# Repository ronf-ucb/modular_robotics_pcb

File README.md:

modular_robotics_pcb
====================

Board designs for the embedded modular robotics project

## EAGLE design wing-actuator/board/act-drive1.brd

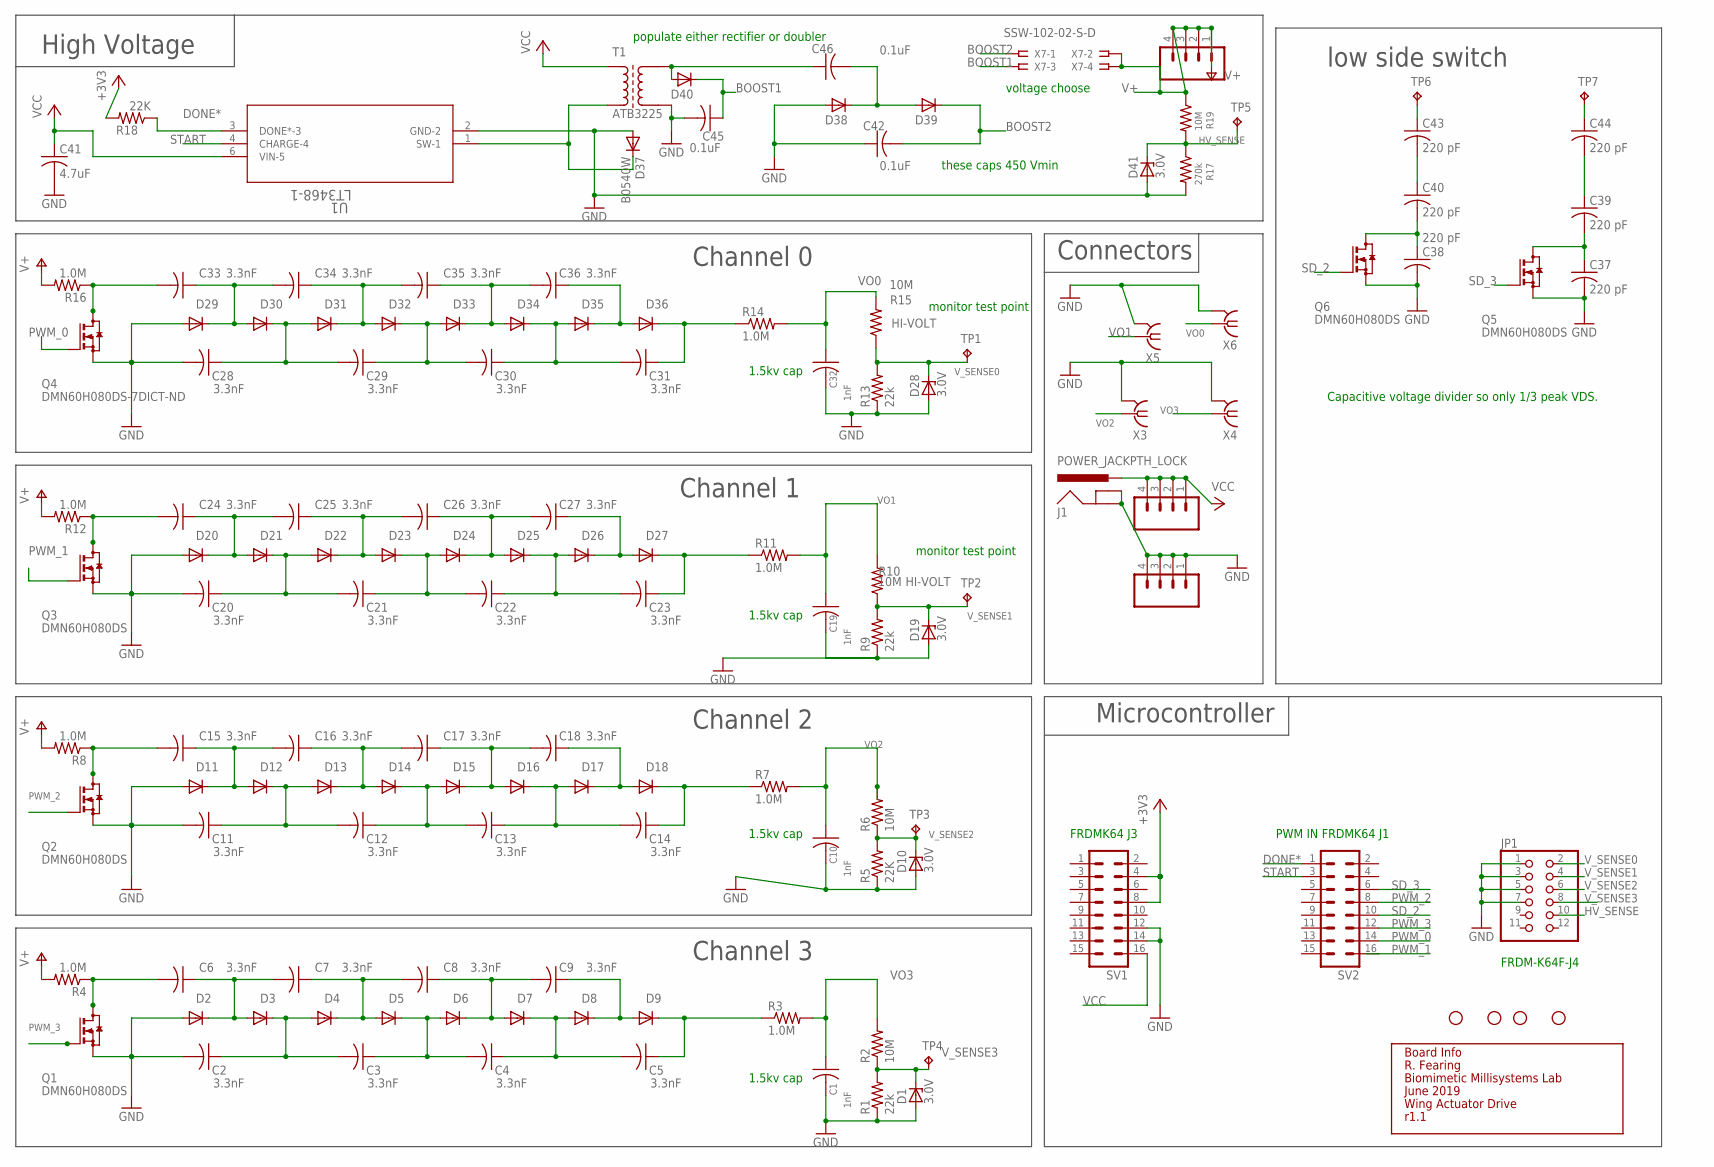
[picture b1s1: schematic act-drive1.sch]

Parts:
C1, C10, C19, C32: 1nF; C1206; DIGIKEY 399-7078-1-ND
C2, C3, C4, C5, C6, C7, C8, C9, C11, C12, C13, C14, C15, C16, C17, C18, C20, C21, C22, C23, C24, C25, C26, C27, C28, C29, C30, C31, C34, C35, C36: 3.3nF; C0805K
C33: 3.3nF; C0805K; DIGIKEY 399-5576-1-ND
C37, C38, C39, C40, C43, C44: 220 pF; C1206; DIGIKEY 311-4469-1-ND
C41: 4.7uF; C1206; DIGIKEY 399-1265-1-ND
C42, C45, C46: 0.1uF; C1206; DIGIKEY 445-7758-1-ND
D1, D10, D19: 3.0V; SOD80C
D2, D3, D4, D5, D6, D7, D8, D9, D11, D12, D13, D14, D15, D16, D17, D22, D23, D25, D26, D27, D30, D31, D32, D33, D34, D35, D36, D38, D39, D40: DIODE-SOD323-W; SOD323-W
D18, D20, D21, D24, D29: DIODE-SOD323-W; SOD323-W; DIGIKEY DA2JF8100LCT-ND
D28, D41: 3.0V; SOD80C; DIGIKEY MM3Z3V0ST1GOSCT-ND
D37: B0540W; SOD123; DIGIKEY B0540W-FDICT-ND
H1, H2, H3, H4: STAND-OFFTIGHT; STAND-OFF-TIGHT
I1: INFO
J1: POWER_JACKPTH_LOCK; POWER_JACK_PTH_LOCK; DIGIKEY CP-202A-ND
JP1: PINHD-2X6; 2X06
JP2, JP3, JP4: M04LOCK; 1X04_LOCK
Q1, Q2, Q3: BSS123; SOT23; PART# DMN60H080DS
Q4: BSS123; SOT23; DIGIKEY DMN60H080DS-7DICT-ND
Q5, Q6: BSS123; SOT23; PART# DMN60H080DS; DIGIKEY DMN60H080DS-7DICT-ND
R1, R9: 22k; R1206
R2, R6, R10, R15: 10M; R2010; DIGIKEY CHV2010-FX-1005ELFCT-ND
R3, R4, R7, R8, R11, R12, R14, R16: 1.0M; R1206; DIGIKEY P1.0MECT-ND
R5, R18: 22K; R1206
R13: 22k; R1206; DIGIKEY P22KECT-ND
R17: 270k; R1206; DIGIKEY P270KECT-ND
R19: 10M; R1206; DIGIKEY P10MECT-ND
SV1, SV2: ML16; DIGIKEY ED10523-ND
T1: ATB3225; XFMR3225; DIGIKEY 445-8636-1-ND
TP1, TP2, TP3, TP4: TPTP10SQ; TP10SQ
TP5, TP6, TP7: TPTP20SQ; TP20SQ
U1: LT3468-1; TSOT-23_S5; DIGIKEY LT3468ES5#TRMPBFCT-ND
X3, X4, X6: SMA-142-0701-801/806; J502-ND-142-0701-801/806
X5: SMA-142-0701-801/806; J502-ND-142-0701-801/806; DIGIKEY J502-ND
X7: SSW-102-02-S-D

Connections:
+3V3: R18.2, SV1.4, SV1.8
BOOST: C46.2, D38.C, D39.A
BOOST1: C45.1, D40.C, X7.3
BOOST2: C42.2, D39.C, X7.1
DONE*: R18.1, SV2.1, U1.3 (DONE*-3)
GND: C1.2, C2.2, C10.2, C11.2, C19.2, C20.2, C28.2, C32.2, C37.2, C38.2, C41.2, C42.1, C45.2, D1.A, D2.A, D10.A, D11.A, D19.A, D20.A, D28.A, D29.A, D37.A, D38.A, D41.A, J1.GND, J1.GNDBREAK, JP1.1, JP1.3, JP1.5, JP1.7, JP2.1, JP2.2, JP2.3, JP2.4, Q1.2 (S), Q2.2 (S), Q3.2 (S), Q4.2 (S), Q5.2 (S), Q6.2 (S), R1.1, R5.1, R9.1, R13.1, R17.2, SV1.12, SV1.14, T1.S3, U1.2 (GND-2), X3.G@1 (2), X3.G@2 (2), X3.G@3 (2), X3.G@4 (2), X4.G@1 (2), X4.G@2 (2), X4.G@3 (2), X4.G@4 (2), X5.G@1 (2), X5.G@2 (2), X5.G@3 (2), X5.G@4 (2), X6.G@1 (2), X6.G@2 (2), X6.G@3 (2), X6.G@4 (2)
HV_SENSE: D41.C, JP1.10, R17.1, R19.2, TP5.TP
unnamed: C29.1, C30.2, D32.C, D33.A
unnamed: C33.1, C34.2, D29.C, D30.A
unnamed: C31.1, D36.C, R14.1
unnamed: C14.1, D18.C, R7.1
unnamed: C28.1, C29.2, D30.C, D31.A
unnamed: C46.1, D40.A, T1.S2
unnamed: C34.1, C35.2, D31.C, D32.A
unnamed: C33.2, Q4.3 (D), R16.1
unnamed: C23.1, D27.C, R11.1
unnamed: C35.1, C36.2, D33.C, D34.A
unnamed: C24.1, C25.2, D20.C, D21.A
unnamed: D37.C, T1.P4, U1.1 (SW-1)
unnamed: C20.1, C21.2, D21.C, D22.A
unnamed: C27.1, D26.C, D27.A
unnamed: C21.1, C22.2, D23.C, D24.A
unnamed: C22.1, C23.2, D25.C, D26.A
unnamed: C15.1, C16.2, D11.C, D12.A
unnamed: C11.1, C12.2, D12.C, D13.A
unnamed: C18.1, D17.C, D18.A
unnamed: C25.1, C26.2, D22.C, D23.A
unnamed: C26.1, C27.2, D24.C, D25.A
unnamed: C24.2, Q3.3 (D), R12.1
unnamed: C12.1, C13.2, D14.C, D15.A
unnamed: C13.1, C14.2, D16.C, D17.A
unnamed: C5.1, D9.C, R3.1
unnamed: C16.1, C17.2, D13.C, D14.A
unnamed: C17.1, C18.2, D15.C, D16.A
unnamed: C15.2, Q2.3 (D), R8.1
unnamed: C6.1, C7.2, D2.C, D3.A
unnamed: C2.1, C3.2, D3.C, D4.A
unnamed: C9.1, D8.C, D9.A
unnamed: C3.1, C4.2, D5.C, D6.A
unnamed: C4.1, C5.2, D7.C, D8.A
unnamed: C7.1, C8.2, D4.C, D5.A
unnamed: C8.1, C9.2, D6.C, D7.A
unnamed: C6.2, Q1.3 (D), R4.1
unnamed: C43.1, TP6.TP
unnamed: C40.1, C43.2
unnamed: C38.1, C40.2, Q6.3 (D)
unnamed: C44.1, TP7.TP
unnamed: C39.1, C44.2
unnamed: C37.1, C39.2, Q5.3 (D)
unnamed: C36.1, D35.C, D36.A
unnamed: C30.1, C31.2, D34.C, D35.A
PWM_0: Q4.1 (G), SV2.14
PWM_1: Q3.1 (G), SV2.16
PWM_2: Q2.1 (G), SV2.8
PWM_3: Q1.1 (G), SV2.12
SD_2: Q6.1 (G), SV2.10
SD_3: Q5.1 (G), SV2.6
START: SV2.3, U1.4 (CHARGE-4)
V+: JP4.1, JP4.2, JP4.3, JP4.4, R4.2, R8.2, R12.2, R16.2, R19.1, X7.2, X7.4
VCC: C41.1, J1.PWR, JP3.1, JP3.2, JP3.3, JP3.4, SV1.16, T1.P1, U1.6 (VIN-5)
VO0: C32.1, R14.2, R15.2, X6.1
VO1: C19.1, R10.2, R11.2, X5.1
VO2: C10.1, R6.2, R7.2, X3.1
VO3: C1.1, R2.2, R3.2, X4.1
V_SENSE0: D28.C, JP1.2, R13.2, R15.1, TP1.TP
V_SENSE1: D19.C, JP1.4, R9.2, R10.1, TP2.TP
V_SENSE2: D10.C, JP1.6, R5.2, R6.1, TP3.TP
V_SENSE3: D1.C, JP1.8, R1.2, R2.1, TP4.TP

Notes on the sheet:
High Voltage
Channel 0
Channel 1
Channel 2
Channel 3
Microcontroller
Connectors
PWM IN FRDMK64 J1
FRDM-K64F-J4
monitor test point
FRDMK64 J3
populate either rectifier or doubler
low side switch
Capacitive voltage divider so only 1/3 peak VDS.
voltage choose
these caps 450 Vmin
1.5kv cap

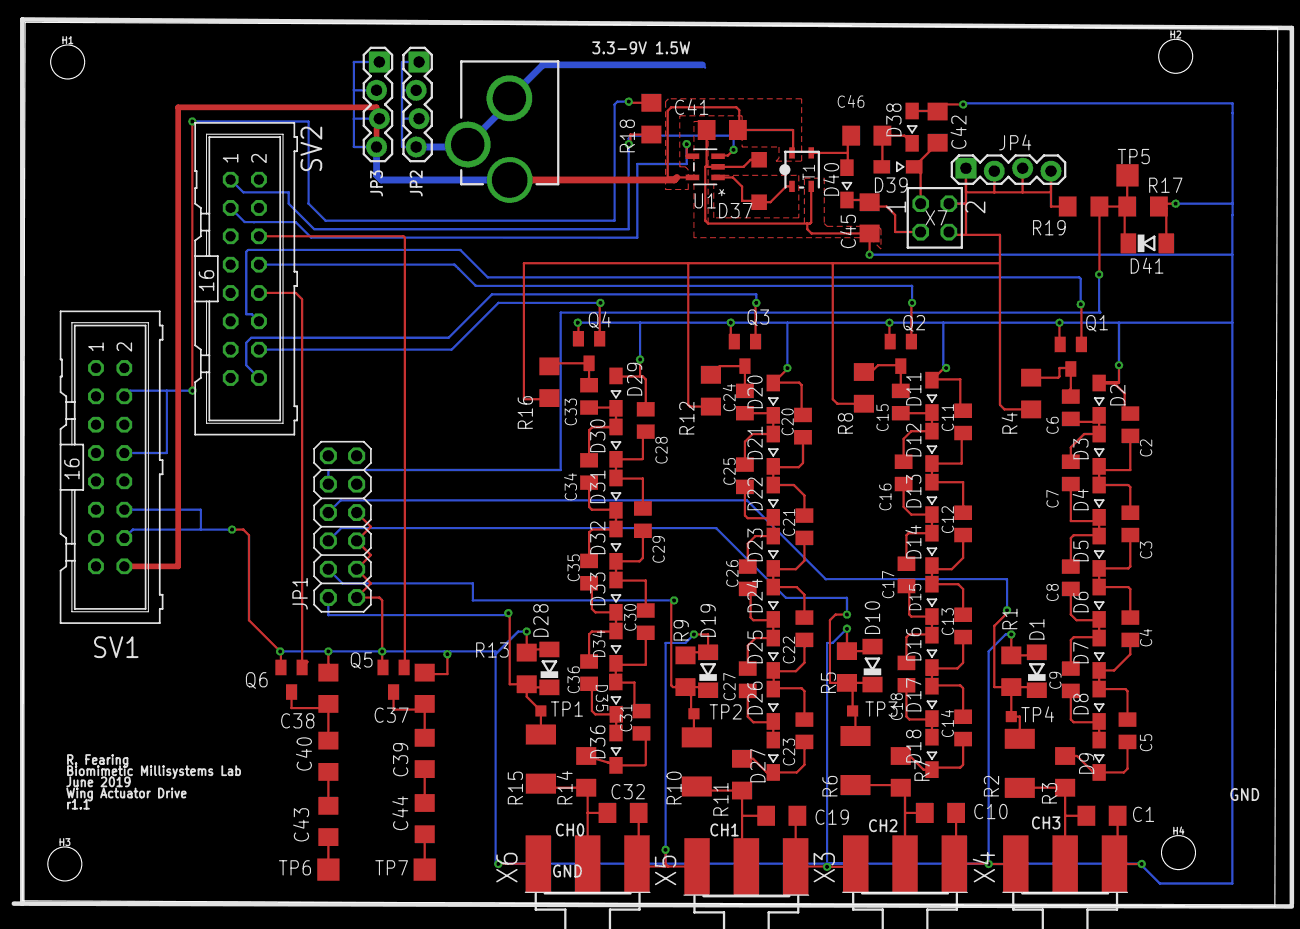
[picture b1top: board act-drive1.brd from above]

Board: 2 copper layers, 112.5 x 79.2 mm, 138 parts (0 on the bottom side), 68 nets.

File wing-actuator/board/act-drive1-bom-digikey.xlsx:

Qty | Value | Device | Package | Parts | Description | DIGIKEY | MOUSER
35 |  | DIODE-SOD323-W | SOD323-W | D2, D3, D4, D5, D6, D7, D8, D9, D11, D12, D13, D14, D15, D16, D17, D18,D19,D20,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 | DIODE | DA2JF8100LCT-ND
5 | 3.0V | ZENER-DIODESOD80C | SOD80C | D1, D10, D19, D28, D41 | Z-Diode | MM3Z3V0ST1GOSCT-ND
1 | B0540W | DIODE-SOD123 | SOD123 | D37 | DIODE | B0540W-FDICT-ND
8 | 1.0M | R-US_R1206 | R1206 | R3, R4, R7, R8, R11, R12, R14, R16 | RESISTOR, American symbol | P1.0MECT-ND
1 | 10M | R-US_R1206 | R1206 | R19 | RESISTOR, American symbol | P10MECT-ND
4 | 10M | R-US_R2010 | R2010 | R2, R6, R10, R15 | RESISTOR, American symbol | CHV2010-FX-1005ELFCT-ND
5 | 22K | R-US_R1206 | R1206 | R5, R18, R1, R9, R13 | RESISTOR, American symbol | P22KECT-ND
1 | 270k | R-US_R1206 | R1206 | R17 | RESISTOR, American symbol | P270KECT-ND
3 | 0.1uF 450V | C-USC1206 | C1206 | C42, C45, C46 | CAPACITOR, American symbol | 445-7758-1-ND
4 | 1nF 1k5V | C-USC1206 | C1206 | C1, C10, C19, C32 | CAPACITOR, American symbol | 399-7078-1-ND
6 | 220 pF, 1000V | C-USC1206 | C1206 | C37, C38, C39, C40, C43, C44 | CAPACITOR, American symbol | 311-4469-1-ND
32 | 3.3nF | C-USC0805K | C0805K | C2, C3, C4, C5, C6, C7, C8, C9, C11, C12, C13, C14, C15, C16, C17, C18, C20, C2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 | CAPACITOR, American symbol | 399-5576-1-ND
1 | 4.7uF | C-USC1206 | C1206 | C41 | CAPACITOR, American symbol | 399-1265-1-ND
1 | ATB3225 | ATB3225 | XFMR3225 | T1 | TDK ATB3225 xfmr 10:1 | 445-8636-1-ND
6 | BSS123 | BSS123 | SOT23 | Q1, Q2, Q3,Q4, Q5, Q6 | N-CHANNEL MOS FET | DMN60H080DS-7DICT-ND | 621-DMN60H080DS-7
1 | LT3468-1 | LT3468-1 | TSOT-23_S5 | U1 | Boost Converter | LT3468ES5#TRMPBFCT-ND
2 |  | ML16 | ML16 | SV1, SV2 | CONN HEADER VERT 16POS 2.54MM | ED10523-ND
2 |  |  |  | SV1P, SV2P | 16 Position Cable Assembly Rectangular Socket to Socket 1.50' | H3CCS-1618M-ND
1 | POWER_JACKPTH_LOCK | POWER_JACKPTH_LOCK | POWER_JACK_PTH_LOCK | J1 | Power Jack | CP-202A-ND
4 | SMA-142-0701-801/806 | SMA-142-0701-801/806 | J502-ND-142-0701-801/806 | X3, X4, X5, X6 | SMA 50 Ohm End Launch Jack Receptacle - Round Contact | J502-ND
1 | SSW-102-02-S-D | SSW-102-02-S-D | SSW-102-02-S-D | X7 | THROUGH-HOLE .025 SQ POST SOCKET"
4 | STAND-OFFTIGHT | STAND-OFFTIGHT | STAND-OFF-TIGHT | H1, H2, H3, H4 | Stand Off
4 | TPTP10SQ | TPTP10SQ | TP10SQ | TP1, TP2, TP3, TP4 | Test pad
3 | TPTP20SQ | TPTP20SQ | TP20SQ | TP5, TP6, TP7 | Test pad
3 |  | M04LOCK | 1X04_LOCK | JP2, JP3, JP4 | Header 4
1 |  | PINHD-2X6 | 2X06 | JP1 | PIN HEADER

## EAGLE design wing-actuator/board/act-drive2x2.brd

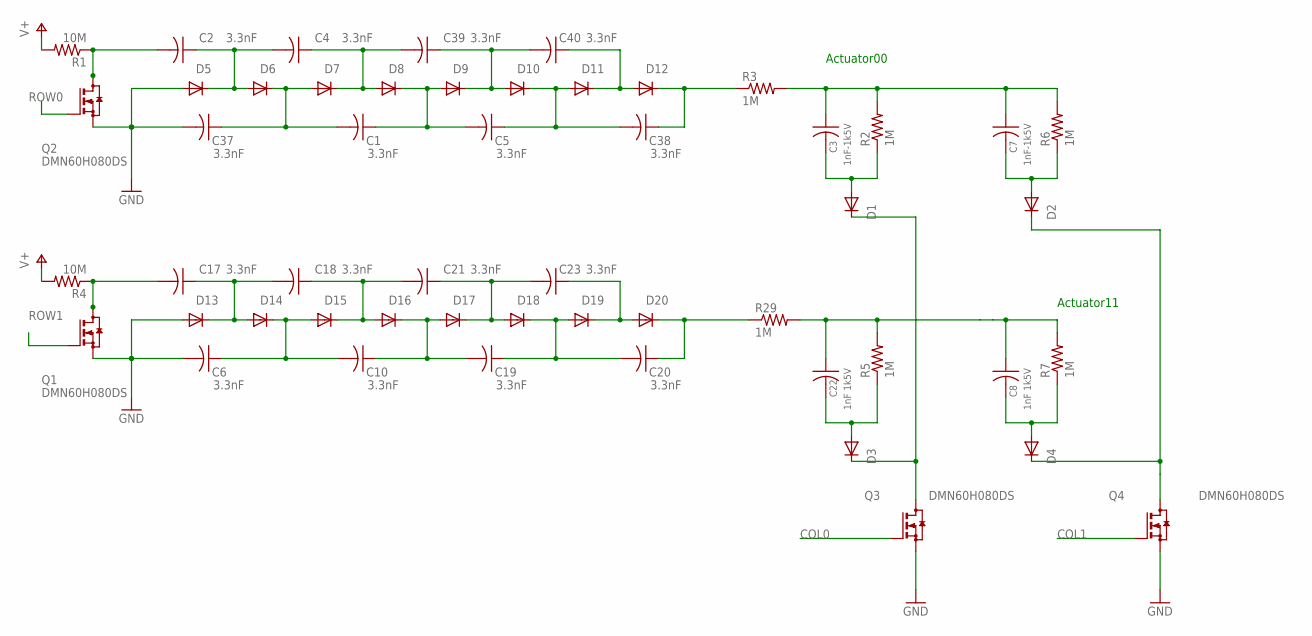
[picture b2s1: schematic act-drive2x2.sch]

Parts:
C1, C2, C4, C5, C6, C10, C17, C18, C19, C20, C21, C23, C37, C38, C39, C40: 3.3nF; C0805K
C3, C7: 1nF-1k5V; C1206
C8, C22: 1nF 1k5V; C1206
D1, D2, D3, D4, D5, D6, D7, D8, D9, D10, D11, D12, D13, D14, D15, D16, D17, D18, D19, D20: DIODE-SOD323-W; SOD323-W
Q1, Q2, Q3, Q4: BSS123; SOT23; PART# DMN60H080DS
R1, R4: 10M; R1206
R2, R3, R5, R6, R7, R29: 1M; R1206

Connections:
COL0: Q3.1 (G)
COL1: Q4.1 (G)
GND: C6.2, C37.2, D5.A, D13.A, Q1.2 (S), Q2.2 (S), Q3.2 (S), Q4.2 (S)
unnamed: C1.1, C5.2, D8.C, D9.A
unnamed: C2.1, C4.2, D5.C, D6.A
unnamed: C38.1, D12.C, R3.1
unnamed: C3.2, D1.A, R2.1
unnamed: C1.2, C37.1, D6.C, D7.A
unnamed: C22.2, D3.A, R5.1
unnamed: C4.1, C39.2, D7.C, D8.A
unnamed: C2.2, Q2.3 (D), R1.1
unnamed: C20.1, D20.C, R29.1
unnamed: C39.1, C40.2, D9.C, D10.A
unnamed: C17.1, C18.2, D13.C, D14.A
unnamed: C7.2, D2.A, R6.1
unnamed: C6.1, C10.2, D14.C, D15.A
unnamed: C23.1, D19.C, D20.A
unnamed: C10.1, C19.2, D16.C, D17.A
unnamed: C19.1, C20.2, D18.C, D19.A
unnamed: C8.2, D4.A, R7.1
unnamed: D1.C, D3.C, Q3.3 (D)
unnamed: D2.C, D4.C, Q4.3 (D)
unnamed: C18.1, C21.2, D15.C, D16.A
unnamed: C21.1, C23.2, D17.C, D18.A
unnamed: C17.2, Q1.3 (D), R4.1
unnamed: C40.1, D11.C, D12.A
unnamed: C5.1, C38.2, D10.C, D11.A
ROW0: Q2.1 (G)
ROW1: Q1.1 (G)
V+: R1.2, R4.2
VO0: C3.1, C7.1, R2.2, R3.2, R6.2
VO1: C8.1, C22.1, R5.2, R7.2, R29.2

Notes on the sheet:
Actuator00
Actuator11

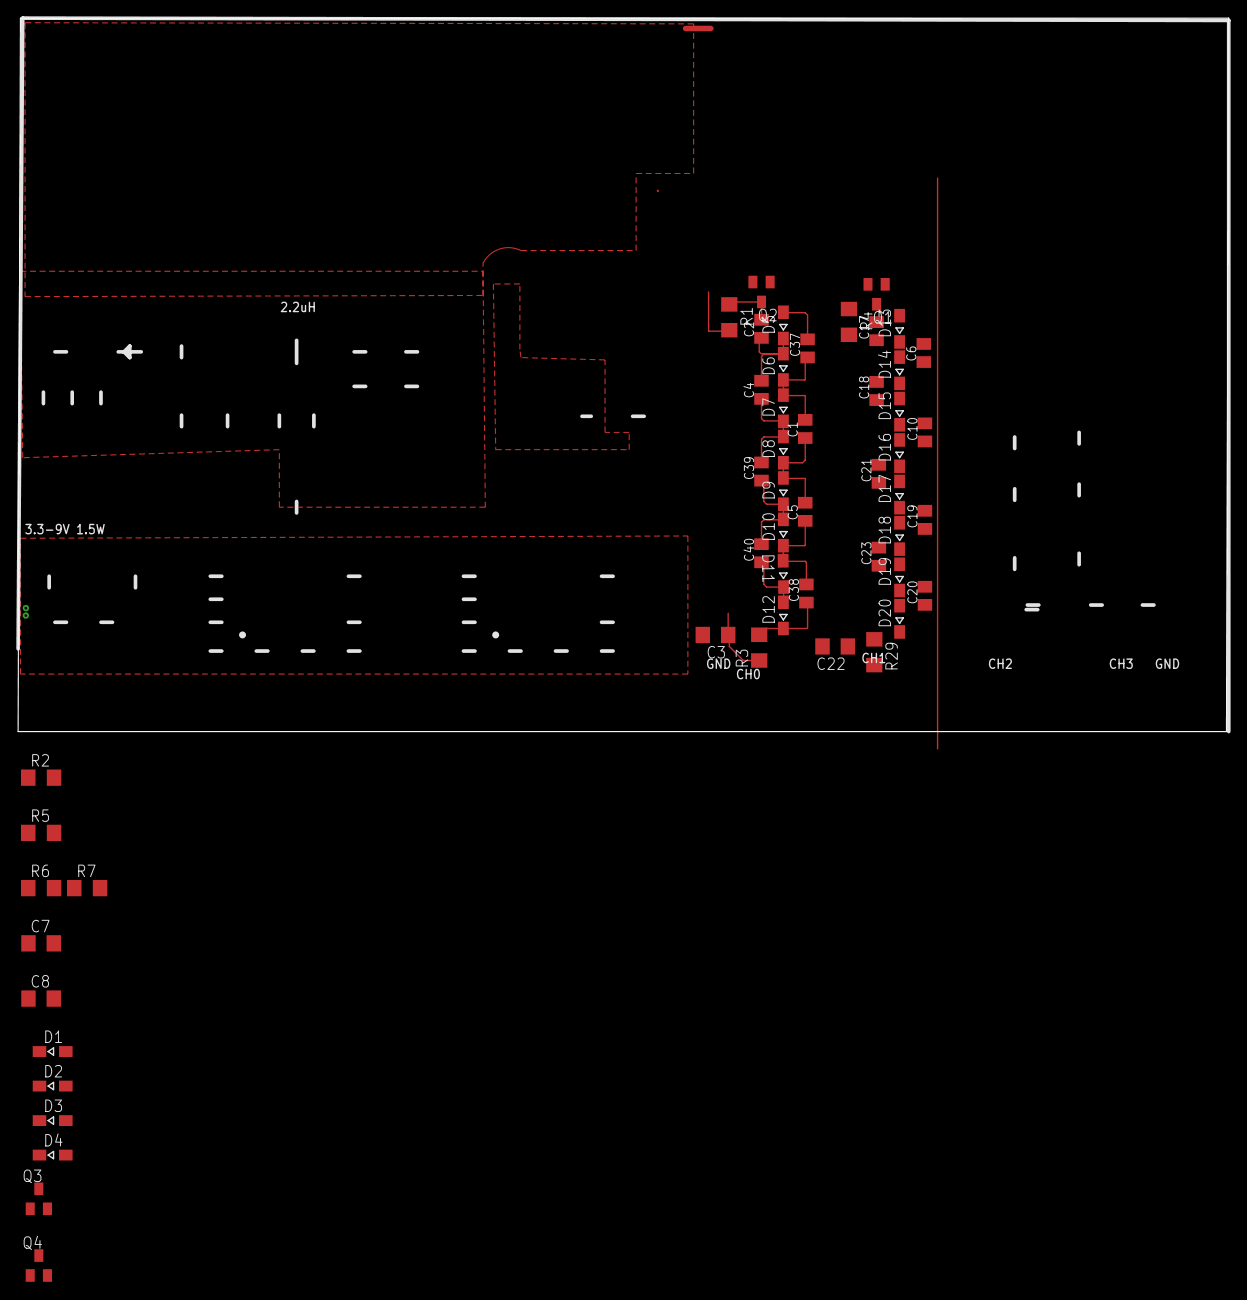
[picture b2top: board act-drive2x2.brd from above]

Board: 2 copper layers, 133.6 x 78.7 mm, 52 parts (0 on the bottom side), 28 nets.

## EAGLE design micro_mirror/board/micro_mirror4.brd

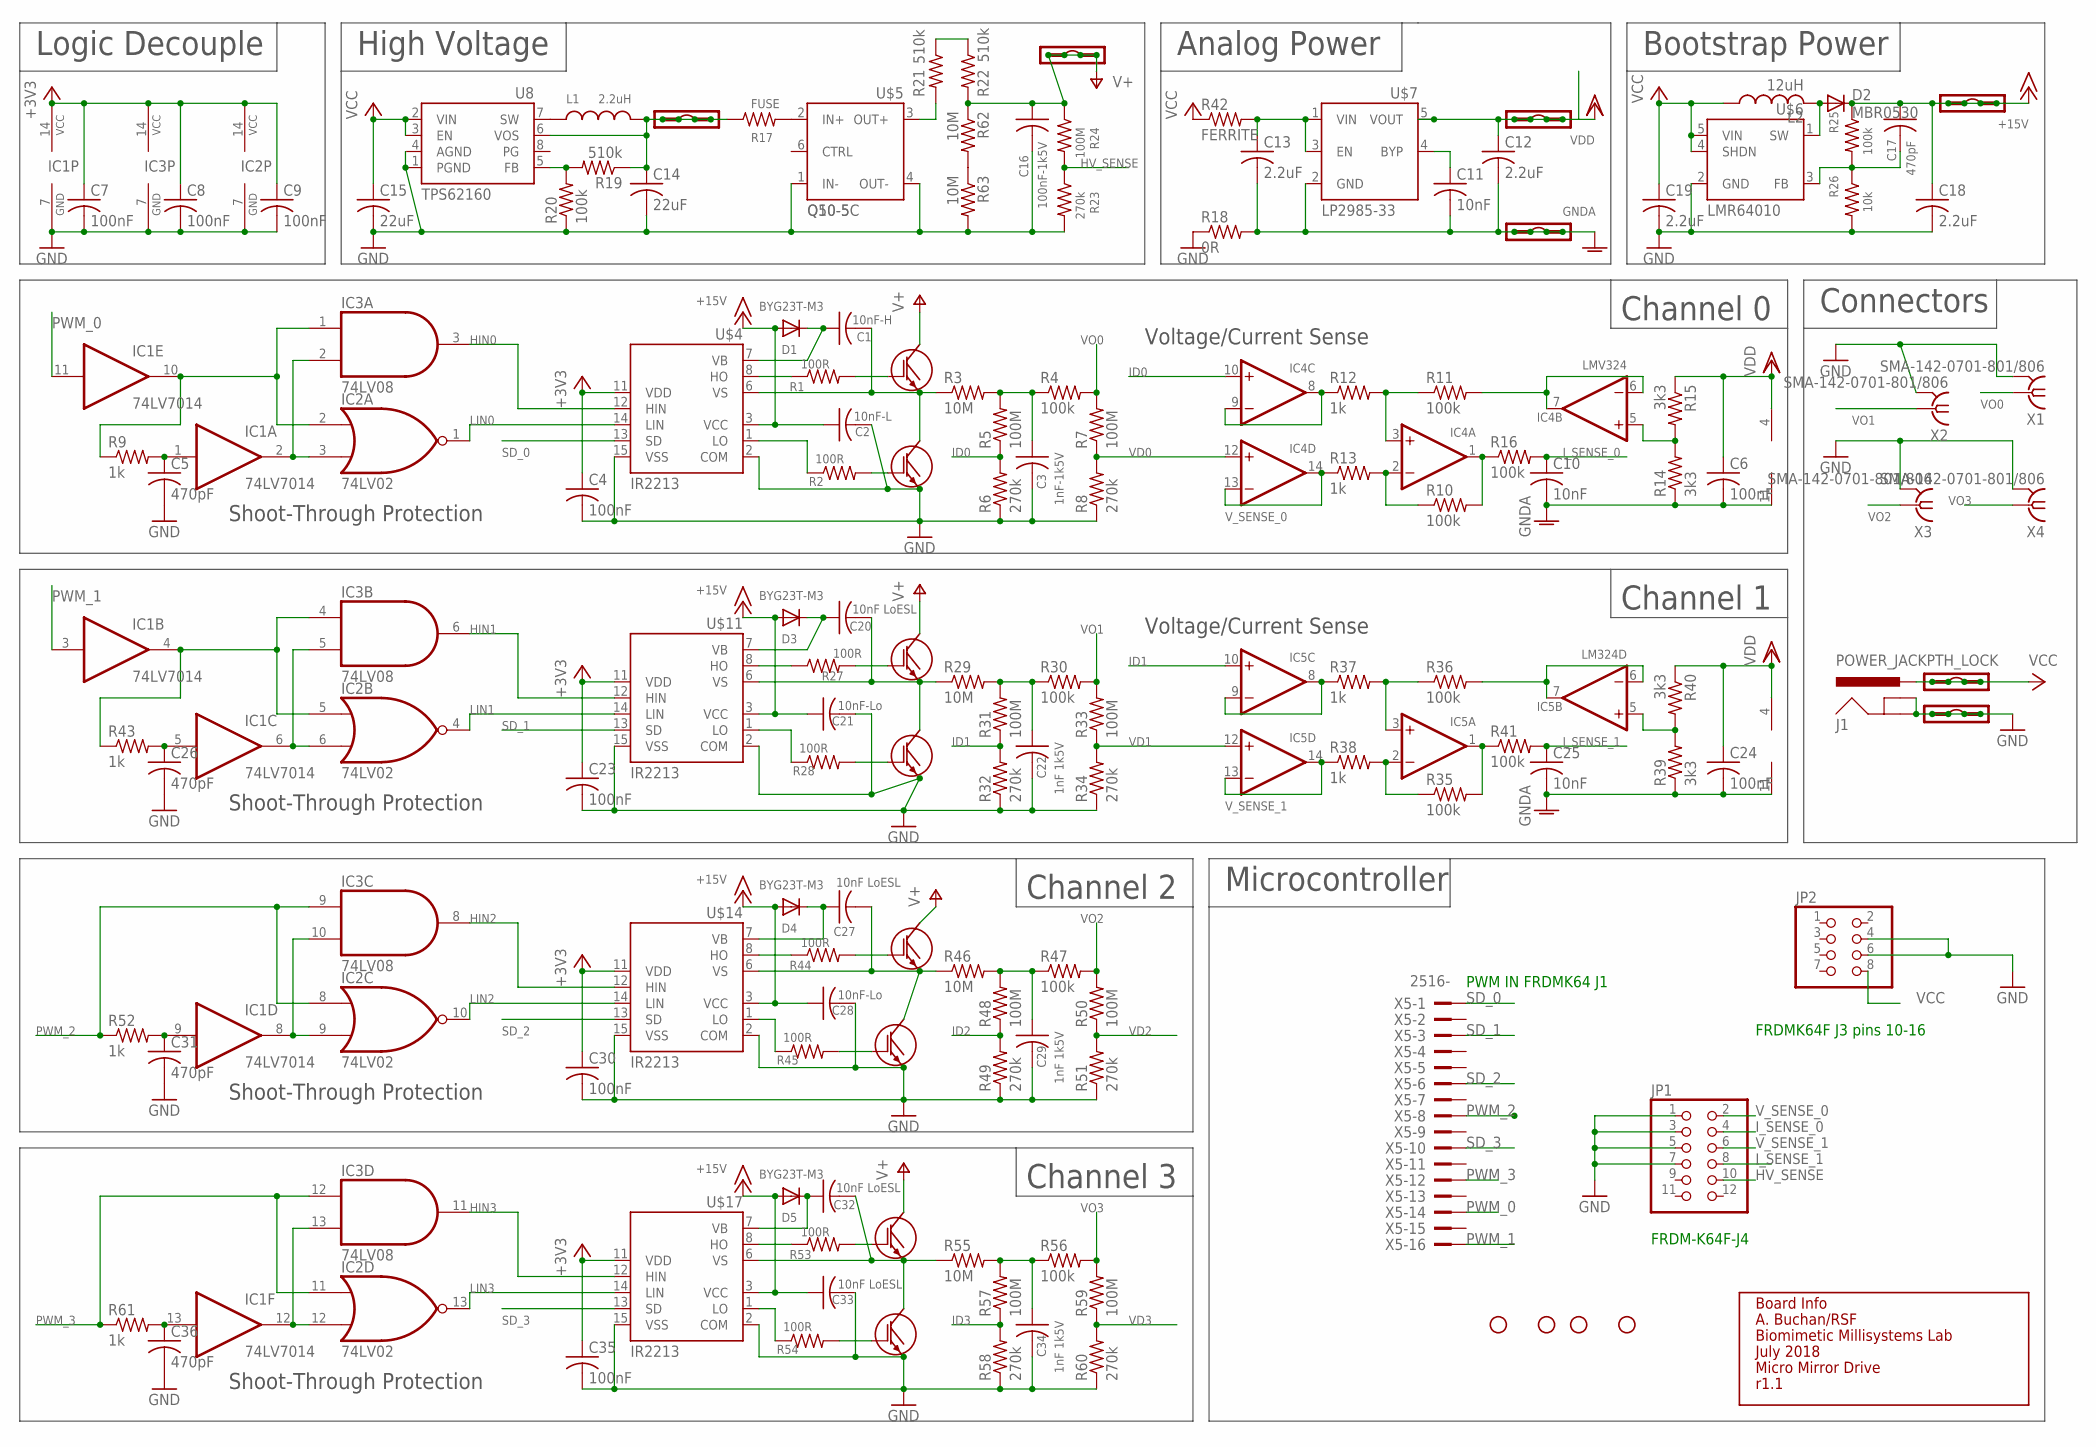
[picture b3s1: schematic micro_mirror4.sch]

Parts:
15V_OUT: M04LOCK; 1X04_LOCK
C1: 10nF-H; C1206
C2: 10nF-L; C1206
C3: 1nF-1k5V; C1206
C4, C6, C7, C8, C9, C23, C24, C30, C35: 100nF; C1206
C5, C17, C26, C31, C36: 470pF; C1206
C10, C11, C25: 10nF; C1206
C12, C13, C18, C19: 2.2uF; C1206
C14, C15: 22uF; C1206
C16: 100nF-1k5V; C2225K
C20, C27, C32, C33: 10nF LoESL; C1206
C21, C28: 10nF-Lo; C1206
C22, C29, C34: 1nF 1k5V; C1206
D1, D3, D4, D5: BYG23T-M3; DO214AC
D2: MBR0530; SOD123
GND: M04LOCK; 1X04_LOCK
GNDA: M04LOCK; 1X04_LOCK
H5, H6, H7, H8: STAND-OFFTIGHT; STAND-OFF-TIGHT
HV_IN: M04LOCK; 1X04_LOCK
HV_OUT: M04LOCK; 1X04_LOCK
IC1: 74LV7014; SO14
IC2: 74LV02; SO14
IC3: 74LV08; SO14
IC4: LMV324; LINEAR_SO14
IC5: LM324D; SO14
J1: POWER_JACKPTH_LOCK; POWER_JACK_PTH_LOCK
JP1: PINHD-2X6; 2X06
JP2: PINHD-2X4; 2X04
L1: 2.2uH; SRN6045
L2: 12uH; L1812
R1, R2, R27, R28, R44, R45, R53, R54: 100R; R1206
R3, R29, R46, R55, R62, R63: 10M; R1206
R4, R10, R11, R16, R20, R25, R30, R35, R36, R41, R47, R56: 100k; R1206
R5, R7, R24, R31, R33, R48, R50, R57, R59: 100M; R1206
R6, R8, R23, R32, R34, R49, R51, R58, R60: 270k; R1206
R9, R12, R13, R37, R38, R43, R52, R61: 1k; R1206
R14, R15, R39, R40: 3k3; R1206
R17: FUSE; R1206
R18: 0R; R1206
R19, R21, R22: 510k; R1206
R26: 10k; R1206
R42: FERRITE; R1206
U8: TPS62160; TSSOP8
U$2, U$3, U$9, U$10, U$12, U$13, U$15, U$16: HGTD1N120BNS; TO252
U$4, U$11, U$14, U$17: IR2213; SO16L
U$5: Q50-5C
U$6: LMR64010; SOT23-5
U$7: LP2985-33; SOT23-5
U$18: INFO
VCC: M04LOCK; 1X04_LOCK
VDDA: M04LOCK; 1X04_LOCK
X1, X2, X3, X4: SMA-142-0701-801/806; J502-ND-142-0701-801/806
X5: 2516-; PAK100/2500-16

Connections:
+15V: 15V_OUT.1, 15V_OUT.2, 15V_OUT.3, 15V_OUT.4, C2.1, C17.1, C18.1, C21.1, C28.1, C33.1, D1.A, D2.C, D3.A, D4.A, D5.A, R25.1, U$4.3 (VCC), U$11.3 (VCC), U$14.3 (VCC), U$17.3 (VCC)
GND: C2.2, C3.2, C4.2, C5.2, C7.2, C8.2, C9.2, C14.2, C15.2, C16.2, C18.2, C19.2, C21.2, C22.2, C23.2, C26.2, C28.2, C29.2, C30.2, C31.2, C33.2, C34.2, C35.2, C36.2, GND.1, GND.2, GND.3, GND.4, IC1.7 (GND), IC2.7 (GND), IC3.7 (GND), J1.GND, J1.GNDBREAK, JP1.1, JP1.3, JP1.5, JP1.7, JP2.4, JP2.6, R6.1, R8.1, R18.1, R20.1, R23.2, R26.2, R32.1, R34.1, R49.1, R51.1, R58.1, R60.1, R63.2, U8.1 (PGND), U8.4 (AGND), U$3.2 (E), U$4.2 (COM), U$4.15 (VSS), U$5.1 (IN-), U$5.4 (OUT-), U$6.2 (GND), U$10.2 (E), U$11.2 (COM), U$11.15 (VSS), U$13.2 (E), U$14.2 (COM), U$14.15 (VSS), U$16.2 (E), U$17.2 (COM), U$17.15 (VSS), X1.G@1 (2), X1.G@2 (2), X1.G@3 (2), X1.G@4 (2), X2.G@1 (2), X2.G@2 (2), X2.G@3 (2), X2.G@4 (2), X3.G@1 (2), X3.G@2 (2), X3.G@3 (2), X3.G@4 (2), X4.G@1 (2), X4.G@2 (2), X4.G@3 (2), X4.G@4 (2)
GNDA: C6.2, C10.2, C11.2, C12.2, C13.2, C24.2, C25.2, GNDA.1, GNDA.2, GNDA.3, GNDA.4, IC4.11 (V-), IC5.11 (V-), R14.1, R18.2, R39.1, U$7.2 (GND)
HIN0: IC3.3 (O), U$4.12 (HIN)
HIN1: IC3.6 (O), U$11.12 (HIN)
HIN2: IC3.8 (O), U$14.12 (HIN)
HIN3: IC3.11 (O), U$17.12 (HIN)
HV_SENSE: JP1.10, R23.1, R24.2
ID0: IC4.10 (+IN), R5.1, R6.2
ID1: IC5.10 (+IN), R31.1, R32.2
ID2: R48.1, R49.2
ID3: R57.1, R58.2
I_SENSE_0: C10.1, JP1.4, R16.2
I_SENSE_1: C25.1, JP1.8, R41.2
LIN0: IC2.1 (O), U$4.14 (LIN)
LIN1: IC2.4 (O), U$11.14 (LIN)
LIN2: IC2.10 (O), U$14.14 (LIN)
LIN3: IC2.13 (O), U$17.14 (LIN)
unnamed: R1.2, U$2.1 (G)
unnamed: R2.2, U$3.1 (G)
unnamed: C1.2, R3.1, U$2.2 (E), U$3.3 (C), U$4.6 (VS)
unnamed: C3.1, R3.2, R4.1, R5.2
unnamed: C1.1, D1.C, U$4.7 (VB)
unnamed: R1.1, U$4.8 (HO)
unnamed: R2.1, U$4.1 (LO)
unnamed: IC1.2 (O), IC2.3 (I1), IC3.2 (I1)
unnamed: IC4.8 (OUT), IC4.9 (-IN), R12.1
unnamed: C5.1, IC1.1 (I), R9.2
unnamed: IC4.1 (OUT), R10.2, R16.1
unnamed: R17.2, U$5.2 (IN+)
unnamed: IC4.2 (-IN), R10.1, R13.2
unnamed: IC4.3 (+IN), R11.1, R12.2
unnamed: IC4.5 (+IN), R14.2, R15.2
unnamed: IC4.6 (-IN), IC4.7 (OUT), R11.2
unnamed: L1.1, U8.7 (SW)
unnamed: C14.1, HV_IN.1, HV_IN.2, HV_IN.3, HV_IN.4, L1.2, R17.1, R19.1, U8.6 (VOS)
unnamed: C11.1, U$7.4 (BYP)
unnamed: R19.2, R20.2, U8.5 (FB)
unnamed: D2.A, L2.2, U$6.1 (SW)
unnamed: R27.2, U$9.1 (G)
unnamed: C17.2, R25.2, R26.1, U$6.3 (FB)
unnamed: R21.1, R22.1
unnamed: R28.2, U$10.1 (G)
unnamed: C20.2, R29.1, U$9.2 (E), U$10.3 (C), U$11.6 (VS)
unnamed: R27.1, U$11.8 (HO)
unnamed: R28.1, U$11.1 (LO)
unnamed: C20.1, D3.C, U$11.7 (VB)
unnamed: C22.1, R29.2, R30.1, R31.2
unnamed: IC5.8 (OUT), IC5.9 (-IN), R37.1
unnamed: IC5.2 (-IN), R35.1, R38.2
unnamed: IC5.3 (+IN), R36.1, R37.2
unnamed: IC5.6 (-IN), IC5.7 (OUT), R36.2
unnamed: IC5.1 (OUT), R35.2, R41.1
unnamed: IC5.5 (+IN), R39.2, R40.2
unnamed: C13.1, R42.2, U$7.1 (VIN), U$7.3 (EN)
unnamed: IC1.6 (O), IC2.6 (I1), IC3.5 (I1)
unnamed: C26.1, IC1.5 (I), R43.2
unnamed: R44.2, U$12.1 (G)
unnamed: R45.2, U$13.1 (G)
unnamed: C27.2, R46.1, U$12.2 (E), U$13.3 (C), U$14.6 (VS)
unnamed: R44.1, U$14.8 (HO)
unnamed: R45.1, U$14.1 (LO)
unnamed: C27.1, D4.C, U$14.7 (VB)
unnamed: C29.1, R46.2, R47.1, R48.2
unnamed: IC1.8 (O), IC2.9 (I1), IC3.10 (I1)
unnamed: R53.2, U$15.1 (G)
unnamed: C31.1, IC1.9 (I), R52.2
unnamed: R54.2, U$16.1 (G)
unnamed: C32.2, R55.1, U$15.2 (E), U$16.3 (C), U$17.6 (VS)
unnamed: R53.1, U$17.8 (HO)
unnamed: R54.1, U$17.1 (LO)
unnamed: C32.1, D5.C, U$17.7 (VB)
unnamed: C34.1, R55.2, R56.1, R57.2
unnamed: IC1.12 (O), IC2.12 (I1), IC3.13 (I1)
unnamed: C36.1, IC1.13 (I), R61.2
unnamed: IC1.4 (O), IC2.5 (I0), IC3.4 (I0), R43.1
unnamed: IC1.10 (O), IC2.2 (I0), IC3.1 (I0), R9.1
unnamed: R21.2, U$5.3 (OUT+)
unnamed: R62.2, R63.1
PWM_0: IC1.11 (I), X5.14
PWM_1: IC1.3 (I), X5.16
PWM_2: IC2.8 (I0), IC3.9 (I0), R52.1, X5.8
PWM_3: IC2.11 (I0), IC3.12 (I0), R61.1, X5.12
SD_0: U$4.13 (SD), X5.1
SD_1: U$11.13 (SD), X5.3
SD_2: U$14.13 (SD), X5.6
SD_3: U$17.13 (SD), X5.10
V+: C16.1, HV_OUT.1, HV_OUT.2, HV_OUT.3, HV_OUT.4, R22.2, R24.1, R62.1, U$2.3 (C), U$9.3 (C), U$12.3 (C), U$15.3 (C)
VCC: C15.1, C19.1, J1.PWR, JP2.8, L2.1, R42.1, U8.2 (VIN), U8.3 (EN), U$6.4 (SHDN), U$6.5 (VIN), VCC.1, VCC.2, VCC.3, VCC.4
VD0: IC4.12 (+IN), R7.1, R8.2
VD1: IC5.12 (+IN), R33.1, R34.2
VD2: R50.1, R51.2
VD3: R59.1, R60.2
VDD: C6.1, C24.1, IC4.4 (V+), IC5.4 (V+), R15.1, R40.1
VDDA: C4.1, C7.1, C8.1, C9.1, C12.1, C23.1, C30.1, C35.1, IC1.14 (VCC), IC2.14 (VCC), IC3.14 (VCC), U$4.11 (VDD), U$7.5 (VOUT), U$11.11 (VDD), U$14.11 (VDD), U$17.11 (VDD), VDDA.1, VDDA.2, VDDA.3, VDDA.4
VO0: R4.2, R7.2, X1.1
VO1: R30.2, R33.2, X2.1
VO2: R47.2, R50.2, X3.1
VO3: R56.2, R59.2, X4.1
V_SENSE_0: IC4.13 (-IN), IC4.14 (OUT), JP1.2, R13.1
V_SENSE_1: IC5.13 (-IN), IC5.14 (OUT), JP1.6, R38.1

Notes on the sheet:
Logic Decouple
High Voltage
Analog Power
Bootstrap Power
Shoot-Through Protection
Voltage/Current Sense
Channel 0
Channel 1
Channel 2
Channel 3
Microcontroller
Connectors
PWM IN FRDMK64 J1
FRDM-K64F-J4
FRDMK64F J3 pins 10-16

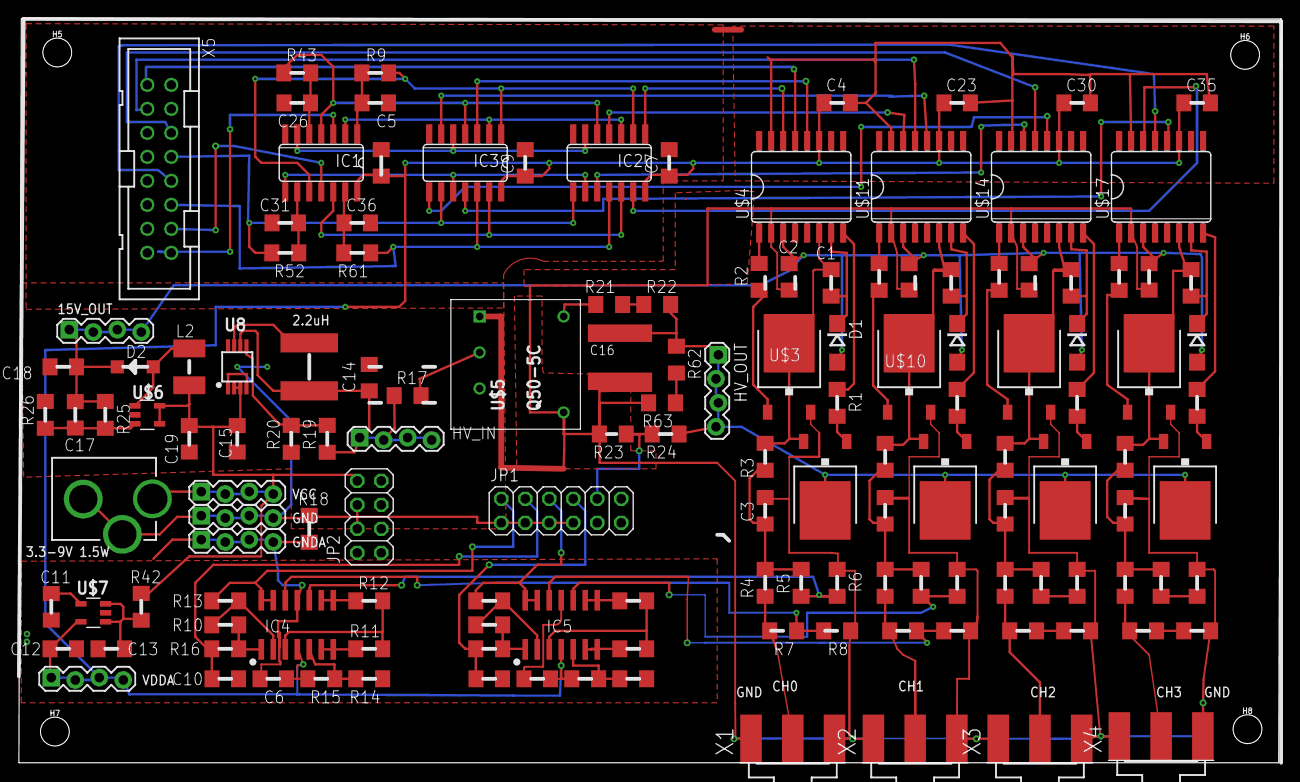
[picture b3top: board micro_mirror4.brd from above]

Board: 2 copper layers, 133.6 x 78.7 mm, 147 parts (0 on the bottom side), 101 nets.

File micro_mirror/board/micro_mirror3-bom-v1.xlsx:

Qty | Value | Device | Package | Parts | Description | AUTHOR | DATE | DESIGN | MF | MPN | OC_FARNELL | OC_NEWARK | Digikey | PROD_ID | REVISION | VERSION
7 |  | M04LOCK | 1X04_LOCK | 15V_OUT, GND, GNDA, HV_IN, HV_OUT, VCC, VDDA | Header 4 |  |  |  |  |  |  |  | 732-5317-ND
1 | 10nF-H | C-USC1206 | C1206 | C1 | CAPACITOR, American symbol |  |  |  |  |  |  |  | 732-12286-1-ND
3 | 10nF | C-USC1206 | C1206 | C10, C11, C25 | CAPACITOR, American symbol |  |  |  |  |  |  |  | 732-12286-1-ND
4 | 2.2uF | C-USC1206 | C1206 | C12, C13, C18, C19 | CAPACITOR, American symbol |  |  |  |  |  |  |  | 1276-3046-1-ND
2 | 22uF | C-USC1206 | C1206 | C14, C15 | CAPACITOR, American symbol |  |  |  |  |  |  |  | 1276-2728-1-ND
1 | 100nF-1k5V | C-USC2225K | C2225K | C16 | CAPACITOR, American symbol |  |  |  |  |  |  |  | 399-10494-1-ND
1 | 10nF-L | C-USC1206 | C1206 | C2 | CAPACITOR, American symbol |  |  |  |  |  |  |  | 732-12286-1-ND
4 | 10nF LoESL | C-USC1206 | C1206 | C20, C27, C32, C33 | CAPACITOR, American symbol |  |  |  |  |  |  |  | 732-12286-1-ND
2 | 10nF-Lo | C-USC1206 | C1206 | C21, C28 | CAPACITOR, American symbol |  |  |  |  |  |  |  | 732-12286-1-ND
4 | 1nF 1k5V | C-USC1206 | C1206 | C3,C22, C29, C34 | CAPACITOR, American symbol |  |  |  |  |  |  |  | 399-7078-1-ND
9 | 100nF | C-USC1206 | C1206 | C4, C6, C7, C8, C9, C23, C24, C30, C35 | CAPACITOR, American symbol |  |  |  |  |  |  |  | 732-8097-1-ND
5 | 470pF | C-USC1206 | C1206 | C5, C26, C31, C36, C17 | CAPACITOR, American symbol |  |  |  |  |  |  |  | 732-8100-1-ND
4 | BYG23T-M3 | DIODE-DO214AC | DO214AC | D1, D3, D4, D5 | DIODE |  |  |  |  |  |  |  | BYG23T-M3/CT-ND
1 | MBR0530 | DIODE-SOD123 | SOD123 | D2 | DIODE |  |  |  |  |  |  |  | MBR0530T3GOSCT-ND
4 | STAND-OFFTIGHT | STAND-OFFTIGHT | STAND-OFF-TIGHT | H5, H6, H7, H8 | Stand Off
1 | 74HC7014 | 7407D | SO14 | IC1 | Hex BUFFER, push-pull high-voltage output |  |  |  |  |  |  |  | 1727-6342-1-ND
1 | 74LV02 | 7402D | SO14 | IC2 | Quad 2-input NOR gate |  |  |  |  |  |  |  | 296-1671-5-ND
1 | 74LV08 | 74S08D | SO14 | IC3 | Quad 2-input AND gate |  |  |  |  |  |  |  | 296-26531-1-ND
2 | LMV324D | LMV324D | SO14 | IC5 | OP AMP |  |  |  |  |  |  |  | 497-13052-1-ND
1 | POWER_JACKPTH_LOCK | POWER_JACKPTH_LOCK | POWER_JACK_PTH_LOCK | J1 | Power Jack |  |  |  |  |  |  |  | CP-202A-ND | PRT-00119
1 |  | PINHD-2X6 | 2X06 | JP1+JP2 | PIN HEADER to be split |  |  |  |  |  |  |  | 609-3221-ND
1 |  | PINHD-2X4 | 2X04 | JP2 | PIN HEADER |  |  |  |  |  |  |  | 609-3221-ND
1 | 2.2uH | INDUCTOR | SRN6045 | L1 |  |  |  |  |  |  |  |  | SRN6045-2R2YCT-ND
1 | 12uH | L-USL1812 | L1812 | L2 | INDUCTOR, American symbol |  |  |  |  |  |  |  | 445-1957-1-ND
8 | 100R | R-US_R1206 | R1206 | R1, R2, R27, R28, R44, R45, R53, R54 | RESISTOR, American symbol |  |  |  |  |  |  |  | P100ECT-ND
4 | 3k3 | R-US_R1206 | R1206 | R14, R15, R39, R40 | RESISTOR, American symbol |  |  |  |  |  |  |  | P3.3KECT-ND
1 | FUSE | R-US_R1206 | R1206 | R17 | RESISTOR, American symbol |  |  |  |  |  |  |  | 507-1806-1-ND
1 | 0R | R-US_R1206 | R1206 | R18 | RESISTOR, American symbol |  |  |  |  |  |  |  | P0.0ECT-ND
1 | 510k | R-US_R1206 | R1206 | R19 | RESISTOR, American symbol |  |  |  |  |  |  |  | P510KECT-ND
1 | 10k | R-US_R1206 | R1206 | R26 | RESISTOR, American symbol |  |  |  |  |  |  |  | P10KECT-ND | P10.0KFCT-ND
4 | 10M | R-US_R1206 | R1206 | R3, R29, R46, R55 | RESISTOR, American symbol |  |  |  |  |  |  |  | P10MECT-ND
12 | 100k | R-US_R1206 | R1206 | R4, R10, R11, R16, R20, R25, R30, R35, R36, R41, R47, R56 | RESISTOR, American symbol |  |  |  |  |  |  |  | P100KECT-ND
1 | FERRITE | R-US_R1206 | R1206 | R42 | RESISTOR, American symbol |  |  |  |  |  |  |  | 732-4628-1-ND
9 | 100M | R-US_R1206 | R1206 | R5, R7, R24, R31, R33, R48, R50, R57, R59 | RESISTOR, American symbol |  |  |  |  |  |  |  | CRHV100MACT-ND
9 | 270k | R-US_R1206 | R1206 | R6, R8, R23, R32, R34, R49, R51, R58, R60 | RESISTOR, American symbol |  |  |  |  |  |  |  | P270KECT-ND
8 | 1k | R-US_R1206 | R1206 | R9, R12, R13, R37, R38, R43, R52, R61 | RESISTOR, American symbol |  |  |  |  |  |  |  | RMCF1206FT1K00CT-ND
1 | INFO | INFO | INFO | U$18 |  | A. Buchan/RSF | 43282 | Micro Mirror Drive |  |  |  |  | Biomimetic Millisystems Lab |  | r1.0
8 | HGTD1N120BNS | HGTD1N120BNS | TO252 | U$2, U$3, U$9, U$10, U$12, U$13, U$15, U$16 |  |  |  |  |  |  |  |  | HGTD1N120BNS9ACT-ND
4 | IR2213 | IR2213 | SO16L | U$4, U$11, U$14, U$17 |  |  |  |  |  |  |  |  | IR2213SPBF-ND
1 | Q10-5 | Q10-5 | Q10-5 | U$5 | Emco Q10-5 |  |  |  |  |  |  |  | 1470-3325-ND
1 | LMR64010 | LMR64010 | SOT23-5 | U$6 | boost converter |  |  |  |  |  |  |  | 296-38771-1-ND
1 | LP2985-33 | LP2985-33 | SOT23-5 | U$7 | buck converter 3.3V |  |  |  |  |  |  |  | 296-18476-1-ND
1 | TPS62160 | TPS62160 | TSSOP8 | U8 | buck adjustable |  |  |  |  |  |  |  | 296-41758-1-ND
4 | SMA-142-0701-801/806 | SMA-142-0701-801/806 | J502-ND-142-0701-801/806 | X1, X2, X3, X4 | SMA 50 Ohm End Launch Jack Receptacle - Round Contact |  |  |  | JOHNSON COMPONENTS | 142-0701-801 | 1608592 | 90F2624 | J502-ND
1 | -2516 | -2516 | PAK100/2500-16 | X5 | 3M (TM) Pak 100 4-Wall Header |  |  |  |  |  | unknown | unknown | ED10535-ND
 |  |  |  | rg58 SMA cable assembly |  |  |  |  |  |  |  |  | ACX1583-ND

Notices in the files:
parts and their libraries:
tag-connect: ©2009 ROFA.cz - modified and updated by Robert Darlington ‹rdarlington@gmail.com›
SparkFun-Passives: Licensing: Creative Commons ShareAlike 4.0 International - https://creativecommons.org/licenses/by-sa/4.0
